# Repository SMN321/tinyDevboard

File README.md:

# tinyDevboard
Prototype of a devboard for the ATtiny85  
Contains connectors for ISP and USB

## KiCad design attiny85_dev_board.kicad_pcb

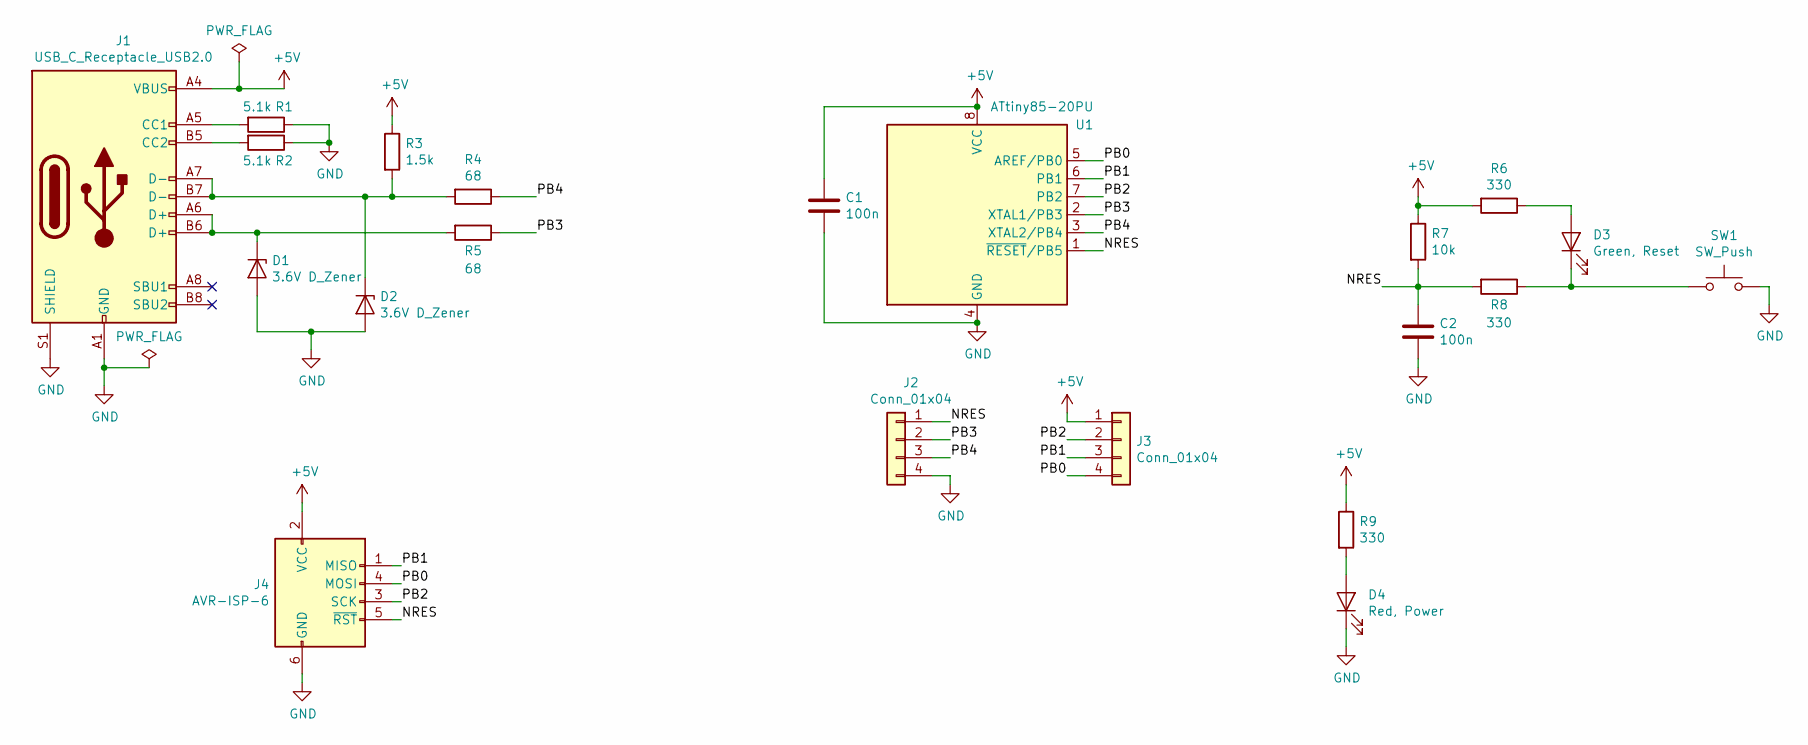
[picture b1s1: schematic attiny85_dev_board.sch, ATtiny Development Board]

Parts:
C1, C2: 100n; C_0805_2012Metric_Pad1.15x1.40mm_HandSolder
D1, D2: 3.6V D_Zener; D_0805_2012Metric_Pad1.15x1.40mm_HandSolder
D3: Green, Reset; LED_0805_2012Metric_Pad1.15x1.40mm_HandSolder
D4: Red, Power; LED_0805_2012Metric_Pad1.15x1.40mm_HandSolder
J1: USB_C_Receptacle_USB2.0; USB_C_Receptacle_GCT_USB4085
J2, J3: Conn_01x04; PinHeader_1x04_P2.54mm_Vertical
J4: AVR-ISP-6; PinHeader_2x03_P2.54mm_Vertical
R1, R2: 5.1k; R_0805_2012Metric_Pad1.15x1.40mm_HandSolder
R3: 1.5k; R_0805_2012Metric_Pad1.15x1.40mm_HandSolder
R4, R5: 68; R_0805_2012Metric_Pad1.15x1.40mm_HandSolder
R6, R8, R9: 330; R_0805_2012Metric_Pad1.15x1.40mm_HandSolder
R7: 10k; R_0805_2012Metric_Pad1.15x1.40mm_HandSolder
SW1: SW_Push; SW_PUSH_6mm
U1: ATtiny85-20PU; DIP-8_W7.62mm_Socket

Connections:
+5V: C1.1, J1.A4 (VBUS), J1.A9 (VBUS), J1.B4 (VBUS), J1.B9 (VBUS), J3.1, J4.2 (VCC), R3.1, R6.2, R7.1, R9.1, U1.8 (VCC)
/NRES: C2.1, J2.1, J4.5 (~RST), R7.2, R8.2, U1.1 (~RESET~/PB5)
/PB0: J3.4, J4.4 (MOSI), U1.5 (AREF/PB0)
/PB1: J3.3, J4.1 (MISO), U1.6 (PB1)
/PB2: J3.2, J4.3 (SCK), U1.7 (PB2)
/PB3: J2.2, R5.1, U1.2 (XTAL1/PB3)
/PB4: J2.3, R4.1, U1.3 (XTAL2/PB4)
GND: C1.2, C2.2, D1.2 (A), D2.2 (A), D4.1 (K), J1.A1 (GND), J1.A12 (GND), J1.B1 (GND), J1.B12 (GND), J1.S1 (SHIELD), J2.4, J4.6 (GND), R1.1, R2.1, SW1.2, U1.4 (GND); also elsewhere on the board
unnamed: D1.1 (K), J1.A6 (D+), J1.B6 (D+), R5.2
unnamed: D2.1 (K), J1.A7 (D-), J1.B7 (D-), R3.2, R4.2
unnamed 10: D3.1 (K), R8.1, SW1.1; also elsewhere on the board
unnamed 11: D3.2 (A), R6.1; also elsewhere on the board
unnamed 12: D4.2 (A), R9.2; also elsewhere on the board
unnamed: J1.A5 (CC1), R1.2
unnamed: J1.B5 (CC2), R2.2

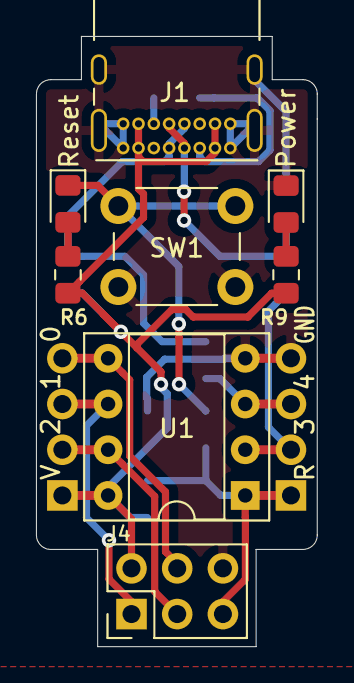
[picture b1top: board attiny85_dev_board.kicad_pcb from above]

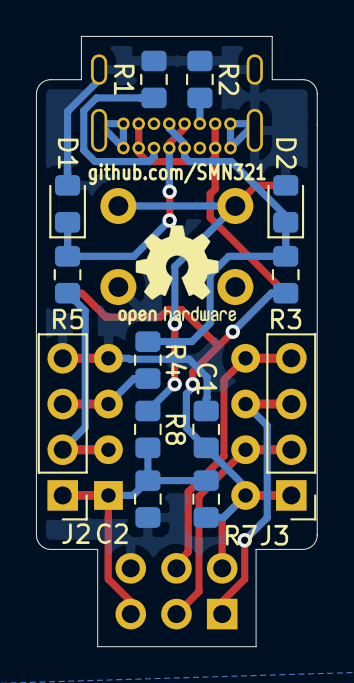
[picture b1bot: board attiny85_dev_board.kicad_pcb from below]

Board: 2 copper layers, 15.6 x 33.9 mm, 21 parts (13 on the bottom side), 15 nets.

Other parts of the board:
Power: Red, Power; LED_0805_2012Metric_Pad1.15x1.40mm_HandSolder
Reset: Green, Reset; LED_0805_2012Metric_Pad1.15x1.40mm_HandSolder

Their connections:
GND: Power.1; also elsewhere on the board
unnamed 10: Reset.1; also elsewhere on the board
unnamed 11: Reset.2; also elsewhere on the board
unnamed 12: Power.2; also elsewhere on the board

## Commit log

2020-03-27 Create LICENSE
